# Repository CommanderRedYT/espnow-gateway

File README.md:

# ESPNow-Gateway
A small PCB + software combo for exposing esp-now via a simple interface.

## PCB Images

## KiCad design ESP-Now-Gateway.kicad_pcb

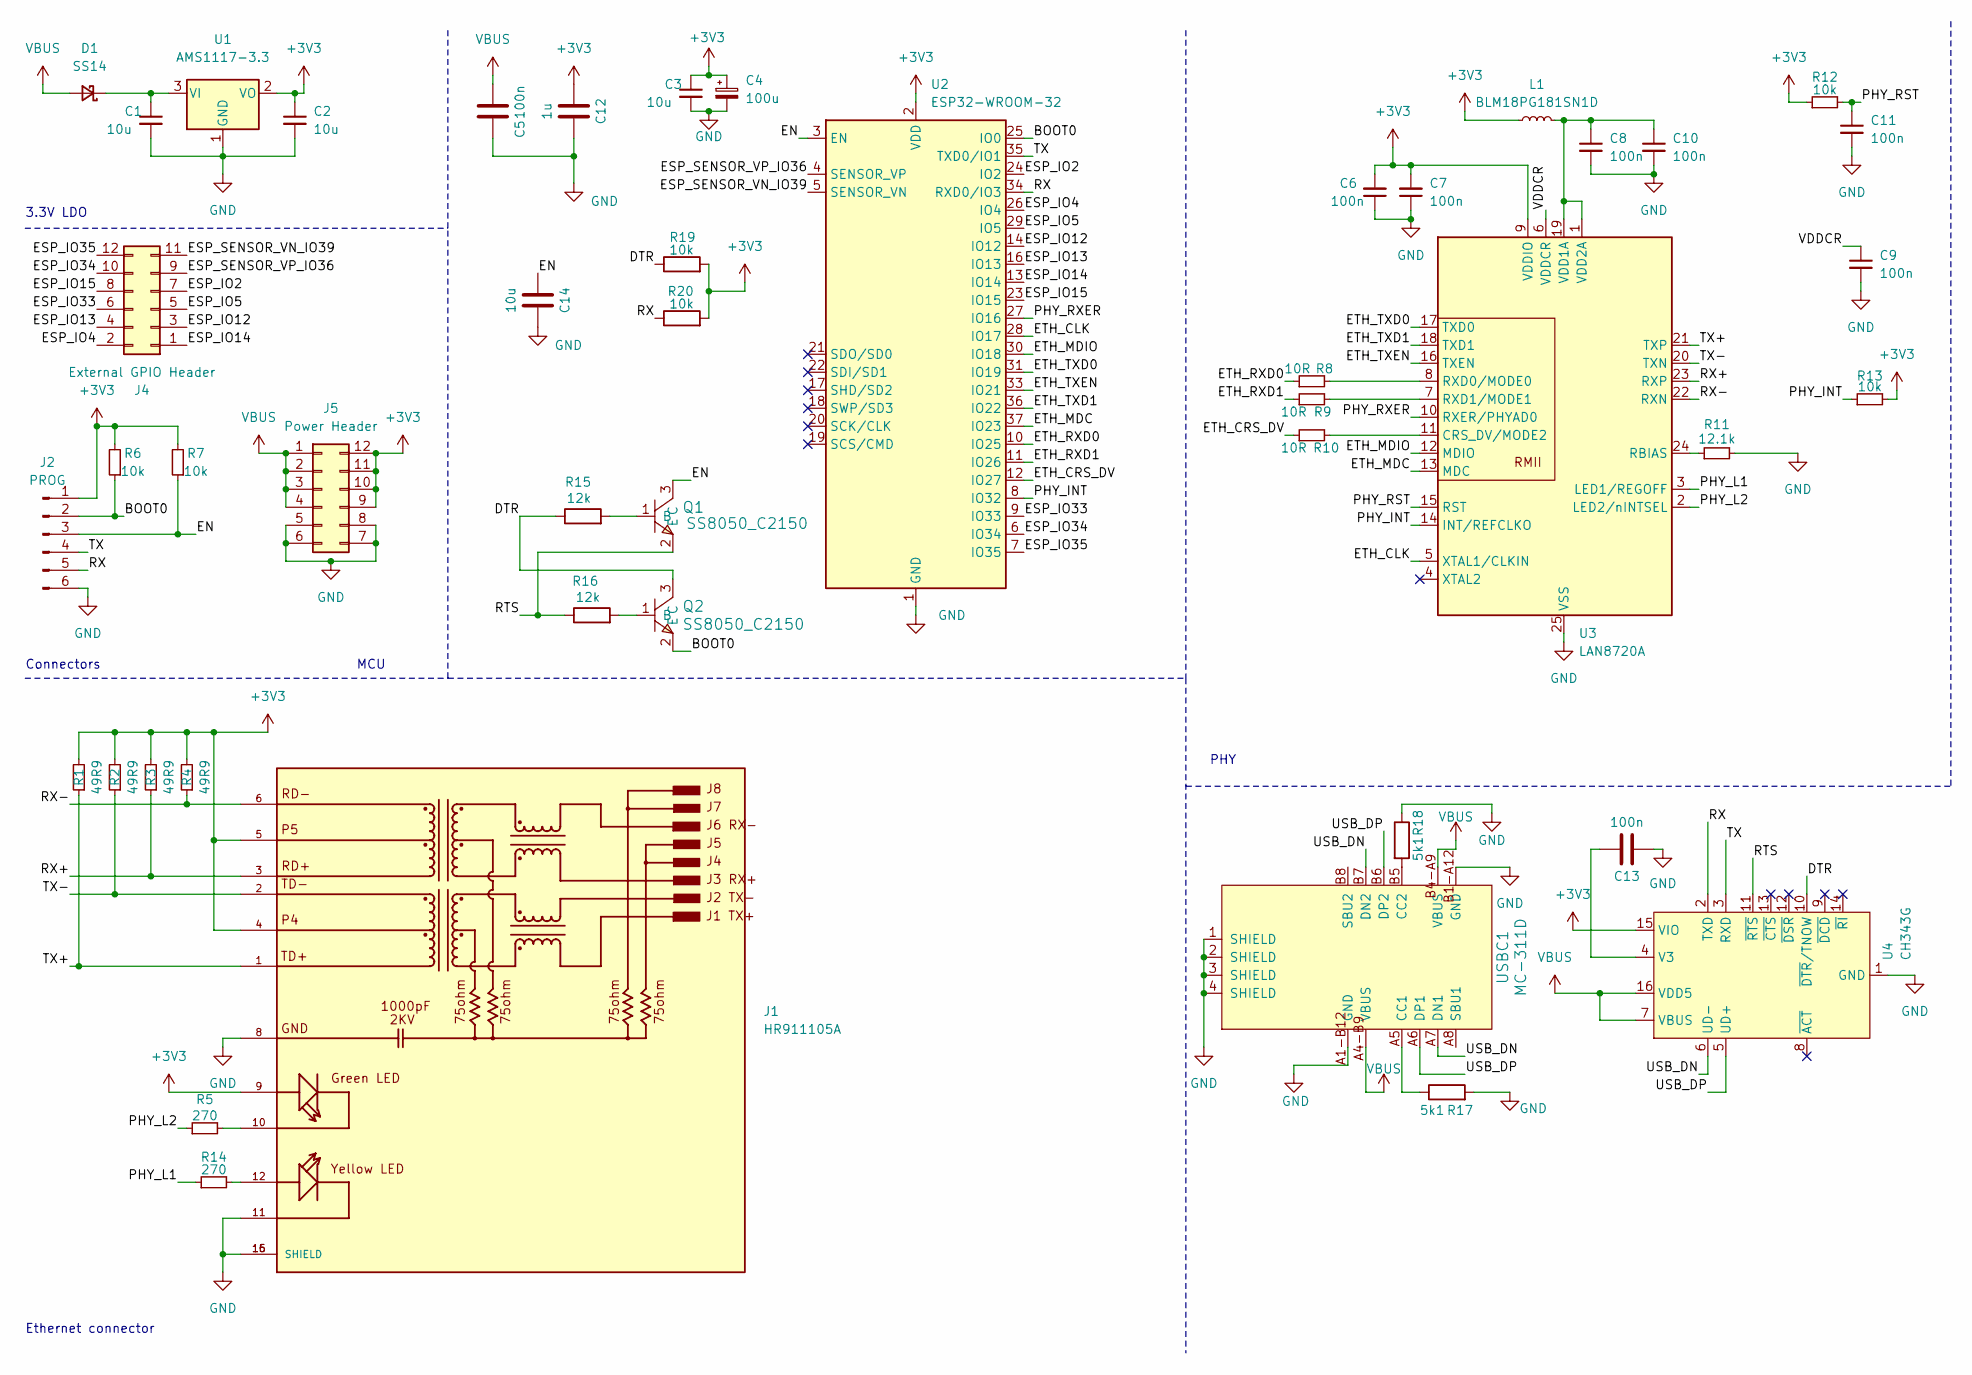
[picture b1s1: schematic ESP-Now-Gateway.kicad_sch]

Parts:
C1: 10u; R_0603_1608Metric
C2, C3: 10u; C_0603_1608Metric
C4: 100u; CP_EIA-3528-21_Kemet-B
C5, C13: 100n; C_0402_1005Metric; LCSC Part # C1525
C6, C7, C8, C9, C10, C11: 100n; C_0603_1608Metric
C12: 1u; C_0603_1608Metric; LCSC Part # C15849
C14: 10u; C_0603_1608Metric; LCSC Part # C96446
D1: SS14; D_SMA
J1: HR911105A; HANRUN_HR911105A; PARTREV A; LCSC Part # C12074
J2: PROG; PinHeader_1x06_P2.54mm_Vertical
J4: External GPIO Header; PinHeader_2x06_P2.54mm_Vertical
J5: Power Header; PinHeader_2x06_P2.54mm_Vertical
L1: BLM18PG181SN1D; R_0603_1608Metric
Q1, Q2: SS8050_C2150; TSOT-23; JLC Part Basic Part
R1, R2, R3, R4: 49R9; R_0603_1608Metric
R5, R14: 270; R_0603_1608Metric
R6, R7, R12, R13, R19, R20: 10k; R_0603_1608Metric
R8, R9, R10: 10R; R_0603_1608Metric
R11: 12.1k; R_0603_1608Metric
R15, R16: 12k; R_0402_1005Metric; LCSC Part # C25752
R17, R18: 5k1; R_0402_1005Metric; LCSC Part # C25905
U1: AMS1117-3.3; SOT-223-3_TabPin2
U2: ESP32-WROOM-32
U3: LAN8720A; QFN-24-1EP_4x4mm_P0.5mm_EP2.6x2.6mm
U4: CH343G; SOIC-16_3.9x9.9mm_P1.27mm; LCSC Part # C2844153
USBC1: MC-311D; USB-C-SMD_MC-311D; JLC Part Extended Part

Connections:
+3V3: C2.1, C3.1, C4.1, C6.2, C7.2, C12.2, J1.4, J1.5, J1.9, J2.1, J5.9, J5.10, J5.11, J5.12, L1.1, R1.2, R2.2, R3.2, R4.2, R6.2, R7.2, R12.1, R13.2, R19.2, R20.2, U1.2 (VO), U2.2 (VDD), U3.9 (VDDIO), U4.15 (VIO)
/BOOT0: J2.2, Q2.2 (E), R6.1, U2.25 (IO0)
/DTR: Q2.3 (C), R15.1, R19.1, U4.10 (~DTR/TNOW)
/EN: C14.2, J2.3, Q1.3 (C), R7.1, U2.3 (EN)
/ESP_IO2: J4.7, U2.24 (IO2)
/ESP_IO4: J4.2, U2.26 (IO4)
/ESP_IO5: J4.5, U2.29 (IO5)
/ESP_IO12: J4.3, U2.14 (IO12)
/ESP_IO13: J4.4, U2.16 (IO13)
/ESP_IO14: J4.1, U2.13 (IO14)
/ESP_IO15: J4.8, U2.23 (IO15)
/ESP_IO33: J4.6, U2.9 (IO33)
/ESP_IO34: J4.10, U2.6 (IO34)
/ESP_IO35: J4.12, U2.7 (IO35)
/ESP_SENSOR_VN_IO39: J4.11, U2.5 (SENSOR_VN)
/ESP_SENSOR_VP_IO36: J4.9, U2.4 (SENSOR_VP)
/ETH_CLK: U2.28 (IO17), U3.5 (XTAL1/CLKIN)
/ETH_CRS_DV: R10.1, U2.12 (IO27)
/ETH_MDC: U2.37 (IO23), U3.13 (MDC)
/ETH_MDIO: U2.30 (IO18), U3.12 (MDIO)
/ETH_RXD0: R8.1, U2.10 (IO25)
/ETH_RXD1: R9.1, U2.11 (IO26)
/ETH_TXD0: U2.31 (IO19), U3.17 (TXD0)
/ETH_TXD1: U2.36 (IO22), U3.18 (TXD1)
/ETH_TXEN: U2.33 (IO21), U3.16 (TXEN)
/PHY_INT: R13.1, U2.8 (IO32), U3.14 (INT/REFCLKO)
/PHY_L1: R14.1, U3.3 (LED1/REGOFF)
/PHY_L2: R5.1, U3.2 (LED2/nINTSEL)
/PHY_RST: C11.1, R12.2, U3.15 (RST)
/PHY_RXER: U2.27 (IO16), U3.10 (RXER/PHYAD0)
/RTS: Q1.2 (E), R16.1, U4.11 (~RTS)
/RX: J2.5, R20.1, U2.34 (RXD0/IO3), U4.2 (TXD)
/RX+: J1.3, R3.1, U3.23 (RXP)
/RX-: J1.6, R4.1, U3.22 (RXN)
/TX: J2.4, U2.35 (TXD0/IO1), U4.3 (RXD)
/TX+: J1.1, R1.1, U3.21 (TXP)
/TX-: J1.2, R2.1, U3.20 (TXN)
/USB_DN: U4.6 (UD-), USBC1.A7 (DN1), USBC1.B7 (DN2)
/USB_DP: U4.5 (UD+), USBC1.A6 (DP1), USBC1.B6 (DP2)
/VDDCR: C9.1, U3.6 (VDDCR)
GND: C1.2, C2.2, C3.2, C4.2, C5.1, C6.1, C7.1, C8.2, C9.2, C10.2, C11.2, C12.1, C13.1, C14.1, J1.8, J1.11, J1.15 (SHIELD), J1.16 (SHIELD), J2.6, J5.5, J5.6, J5.7, J5.8, R11.2, R17.2, R18.1, U1.1 (GND), U2.1 (GND), U2.15 (GND), U2.38 (GND), U2.39 (GND), U3.25 (VSS), U4.1 (GND), USBC1.1 (SHIELD), USBC1.2 (SHIELD), USBC1.3 (SHIELD), USBC1.4 (SHIELD), USBC1.A1-B12 (GND), USBC1.B1-A12 (GND)
unnamed: C1.1, D1.1 (K), U1.3 (VI)
unnamed: J1.10, R5.2
unnamed: J1.12, R14.2
unnamed: Q1.1 (B), R15.2
unnamed: Q2.1 (B), R16.2
unnamed: R10.2, U3.11 (CRS_DV/MODE2)
unnamed: R11.1, U3.24 (RBIAS)
unnamed: R8.2, U3.8 (RXD0/MODE0)
unnamed: R9.2, U3.7 (RXD1/MODE1)
unnamed: C8.1, C10.1, L1.2, U3.1 (VDD2A), U3.19 (VDD1A)
unnamed: C13.2, U4.4 (V3)
unnamed: R17.1, USBC1.A5 (CC1)
unnamed: R18.2, USBC1.B5 (CC2)
VBUS: C5.2, D1.2 (A), J5.1, J5.2, J5.3, J5.4, U4.7 (VBUS), U4.16 (VDD5), USBC1.A4-B9 (VBUS), USBC1.B4-A9 (VBUS)

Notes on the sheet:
PHY
3.3V LDO
Connectors
Ethernet connector
MCU

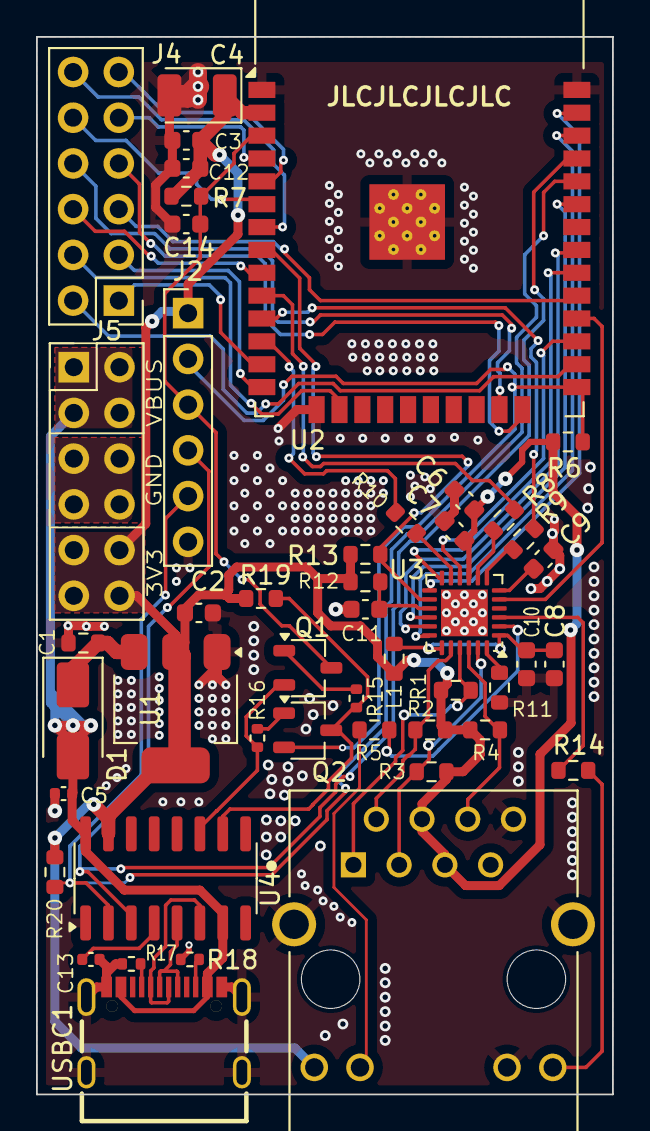
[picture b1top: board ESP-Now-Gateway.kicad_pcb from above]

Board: 2 copper layers, 32.0 x 58.8 mm, 47 parts (0 on the bottom side), 55 nets.

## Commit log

2024-10-23 Semi-finished rework of pcb
2024-10-27 Finalize pcb design
2024-10-28 Improve routing
2024-10-28 More improvements for pcb
2024-10-28 More cleanup
2024-11-02 Improve layout
2024-11-02 Should be production ready
